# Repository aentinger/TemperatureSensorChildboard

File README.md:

💾 Temperatursensor Childboard
==============================

# 📸 Image

# 📂 Description

The LXRobotics Temperature Sensor Childboard offers the possiblity to measure the current temperature with high accuracy. In combination with a Radio Shield a wireless sensor network could be formed for monitoring the temperature in each room of an apartment/house. The thermostat function allows the execution of any action when a preset temperature thresholds is exceeded. For a quick and easy start, an open source Arduino library with sample programs is available.

**Features**

* Temperature range -55 °C to +125 °C
* Thermostat function
* Usage of I2C - only 2 Arduino pins required
* 8 possible I2C addresses configurable via jumpers
* Can be used with the Radioshield the Childboard Adaptershield
* Arduino Library with example programs is available on GitHub

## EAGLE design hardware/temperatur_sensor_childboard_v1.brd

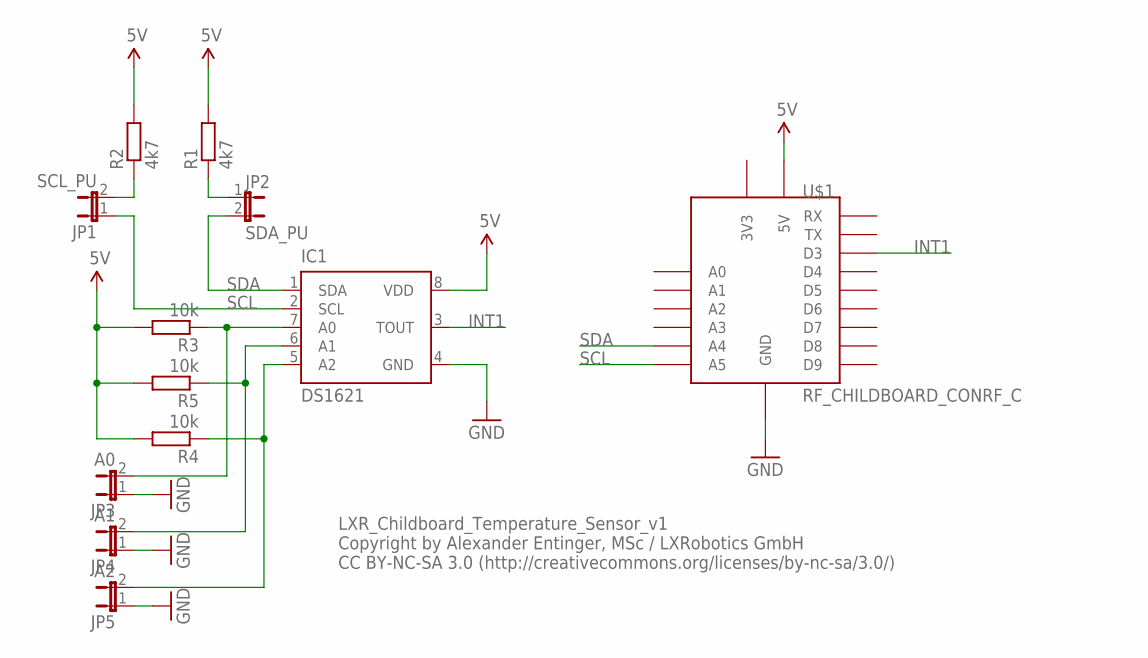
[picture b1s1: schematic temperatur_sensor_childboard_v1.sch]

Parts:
IC1: DS1621; DIL08
JP1: SCL_PU; JP1
JP2: SDA_PU; JP1
JP3: A0; JP1
JP4: A1; JP1
JP5: A2; JP1
R1, R2: 4k7; 0207/7
R3, R4, R5: 10k; 0207/7
U$1: RF_CHILDBOARD_CONRF_C; RF_CHILDBOARD_CON

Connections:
5V: IC1.8 (VDD), R1.2, R2.2, R3.2, R4.2, R5.2, U$1.5V
GND: IC1.4 (GND), JP3.1, JP4.1, JP5.1, U$1.GND, U$1.GND1 (GND), U$1.GND2 (GND)
INT1: IC1.3 (TOUT), U$1.D3
unnamed: JP1.2, R2.1
unnamed: IC1.7 (A0), JP3.2, R3.1
unnamed: JP2.1, R1.1
unnamed: IC1.6 (A1), JP4.2, R5.1
unnamed: IC1.5 (A2), JP5.2, R4.1
SCL: IC1.2 (SCL), JP1.1, U$1.A5
SDA: IC1.1 (SDA), JP2.2, U$1.A4

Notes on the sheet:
LXR_Childboard_Temperature_Sensor_v1 Copyright by Alexander Entinger, MSc / LXRobotics GmbH CC BY-NC-SA 3.0 (http://creativecommons.org/licenses/by-nc-sa/3.0/)

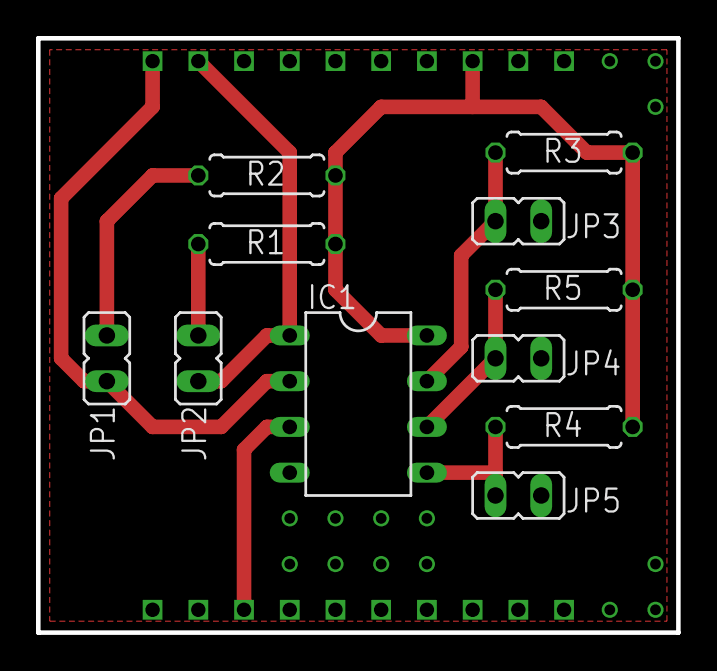
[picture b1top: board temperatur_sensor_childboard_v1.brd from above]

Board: 2 copper layers, 35.6 x 33.0 mm, 12 parts (0 on the bottom side), 10 nets.

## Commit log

2014-01-09 initial checkin of files
2014-01-15 initial checkin of temperatursensor
2017-06-27 Adding hardware + images
2025-03-26 Add BOM.
2025-03-26 Pretty up README.

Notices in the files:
README.md:
License: CC BY-NC-SA 4.0
parts and their libraries:
SparkFun-Aesthetics: Licensing: CC v3.0 Share-Alike You are welcome to use this library for commercial purposes.
